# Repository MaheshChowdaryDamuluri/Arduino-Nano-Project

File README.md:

# ⚡ Custom Arduino Nano Compatible PCB Design Project

Welcome to the official repository for the **Custom Arduino Nano Hardware Clone** project. This repository houses the full programmatic schematic blueprints, advanced multi-layer stackup routing configurations, and fabrication-ready source materials engineered entirely within the KiCad design suite. 

Unlike a standard commercial breakout board, this implementation optimizes power rail stability, enhances differential signal impedance, and introduces precise physical test points for desktop diagnostic verification.

---

## 📐 1. Technical System Architecture

The hardware architecture systematically translates your top-level project settings into specialized component zones designed to reduce trace length and eliminate unwanted parasitic loops:

### 🧠 Core Microcontroller Node (`Arduino nano.kicad_sch`)
* **Processor Unit:** Features a high-performance 8-bit AVR microcontroller housed in an ultra-compact, surface-mount **QFN-32** package footprint.
* **System Clock:** Driven by a precision **16MHz ceramic resonator** (`Murata CSTNE`) to ensure predictable, jitter-free code execution timing.
* **ICSP Header Array:** Breaks out a standard 3-pin In-Circuit Serial Programming (ICSP) interface alongside standard vertical female pin-socket strips for effortless external bootloader flashing and pin mapping.

### 🔌 USB Telemetry & Serial Interface
* **Interface Bridge:** Built around the rugged **FT232RL SSOP-28** USB-to-Serial converter chip, delivering bulletproof stability over long debugging sessions.
* **Upstream Protection:** Protects your computer's USB controller using a resettable surface-mount **0603 Polyfuse** to clamp unexpected short-circuits instantly.
* **Differential Signaling:** Routes raw data lines using precise trace spacing down to test pads (`TP1` and `TP2`) for real-time oscilloscope signal inspection.

### ⚡ Power Supply & Linear Regulation Network
* **DC-DC Step-Down:** Incorporates a dedicated low-dropout (LDO) **LM1117MP-5.0 fixed linear regulator** in a robust SOT-223 package.
* **Filtering Topology:** Employs a multi-stage decoupling matrix combining polarized Tantalum bulk smoothing capacitors ($4.7\mu\text{F}$) with high-frequency $100\text{nF}$ ceramic filtering passives positioned right at the power input boundaries to block supply ripple spikes.
* **Input Isolation:** Implements an internal Schottky reverse-voltage protection diode to safely manage power handover between the external input pin and the desktop USB port.

---

## 🛠️ 2. PCB Layer Stackup & Layout Disciplines

The layout database shifts away from legacy double-sided prototyping to a high-speed **4-layer PCB architecture** configured inside the board setup:

1. **Top Layer (`F.Cu`):** High-density component landing networks and primary signal trace breakouts.
2. **Inner Layer 1 (`In1.Cu`):** Solid Ground Plane (`GND`) serving as a low-impedance return path to significantly reduce EM emissions.
3. **Inner Layer 2 (`In2.Cu`):** Specialized Power Grid distribution plane handling multiple system voltages.
4. **Bottom Layer (`B.Cu`):** Secondary routing pathways and clear status indicators.

* **🎨 Solder Mask Aesthetic:** Formatted for a sleek, premium **Blue Solder Mask** application over high-grade FR4 core material.
* **🚦 Status LEDs:** Incorporates four surface-mount visual telemetry indicators (Yellow for Power tracking, Green for Reset lines, and Red/Green options for system notifications).

---

## 📋 3. Project Bill of Materials (BOM)

| Designator | Component Quantity | Component Value | Package Footprint | Purpose / Function |
| :--- | :---: | :--- | :--- | :--- |
| **U1** | 1 | MCU Core Chip | QFN-32-1EP (5x5mm) | Primary Microcontroller Core |
| **U3** | 1 | FT232RL | SSOP-28_5.3x10.2mm | USB to Serial Communication Bridge |
| **U2** | 1 | LM1117MP-5.0 | SOT-223-3 (TabPin2) | +5V Low-Dropout Regulator |
| **F1** | 1 | Polyfuse (0603) | D_0603_1608Metric | Resettable Overcurrent Protection |
| **Y1** | 1 | 16MHz Resonator | CSTxExxV-3Pin (3.0x1.1mm) | Core Clock Source Oscillator |
| **J1** | 1 | USB_B_Mini | USB_Mini-B_Horizontal | System Power & Programming Interface |
| **SW1** | 1 | SW_Push | Panasonic_EVQPUK_EVQPUB | Master Hardware Reset Button |
| **C4, C9** | 2 | 4u7_16V | CP_EIA-3216-10_Kemet-I | Polarized Tantalum Smoothing Capacitors |
| **C1, C2, C5, C6** | 4 | 1u | C_0603_1608Metric | Ceramic Decoupling Passives |
| **C3, C7, C8, C10** | 4 | 100n | C_0603_1608Metric | High-Frequency Bypass Capacitors |
| **R1 - R7** | 7 | 1k | D_0603_1608Metric | Current Limiting Resistors |
| **D1 - D5** | 5 | LED Colors | LED_0805_2012Metric | Telemetry & Visual Status Indicators |

---

## 📂 4. Repository File Directory
```text
├── Arduino nano.kicad_pro    # Master project settings linking schematics & board layers
├── Arduino nano.kicad_sch    # Top-level interactive hardware electrical schema
├── Arduino nano.kicad_pcb    # Completed physical 4-layer trace layout matrix
├── Arduino nano.kicad_prl    # Project local display preferences & monitor settings
├── .gitignore                # Automatically generated rule patterns filtering out bak files
└── LICENSE                   # MIT Open-Source Hardware Licensing certification

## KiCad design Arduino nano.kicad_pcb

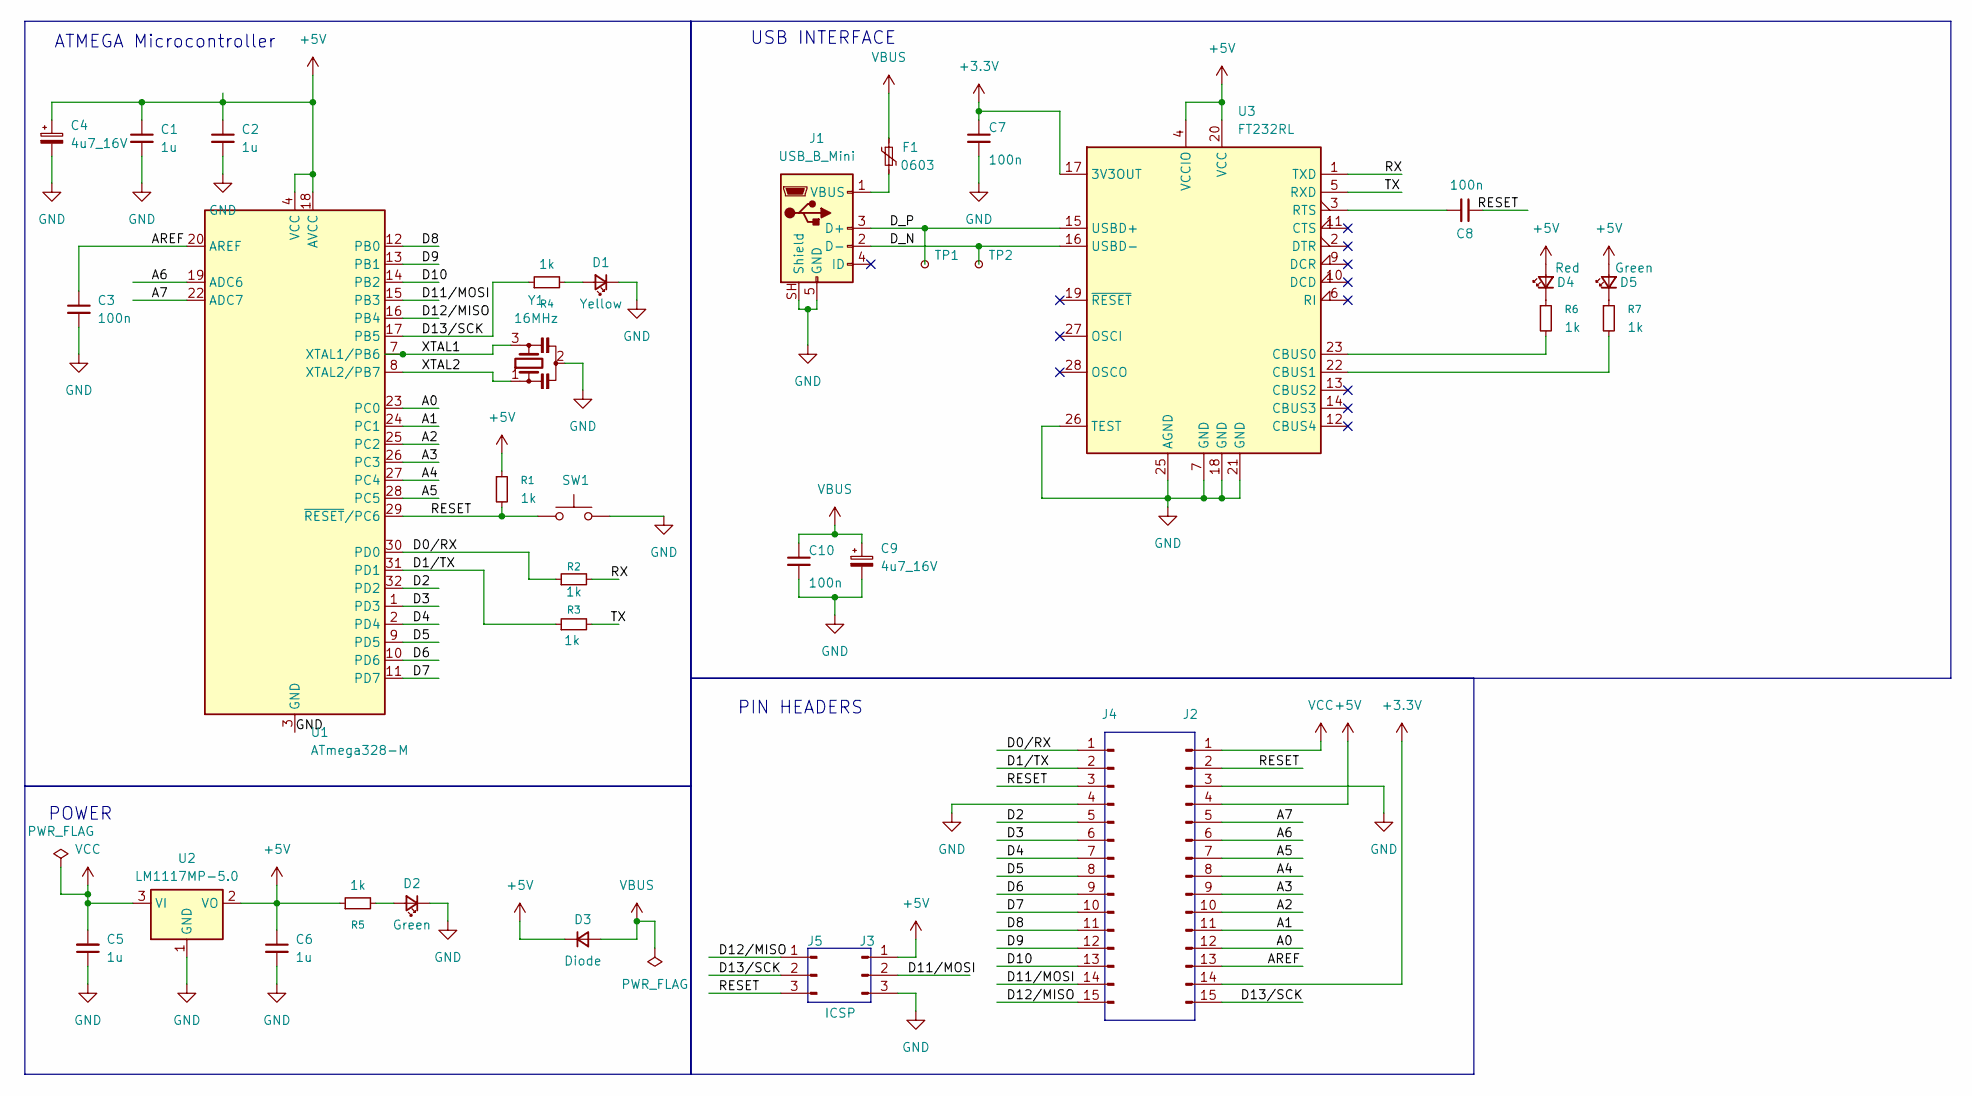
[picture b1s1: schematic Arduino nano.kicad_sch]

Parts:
C1, C2, C5, C6: 1u; C_0603_1608Metric
C3, C7, C8, C10: 100n; C_0603_1608Metric
C4, C9: 4u7_16V; CP_EIA-3216-10_Kemet-I
D1: Yellow; LED_0805_2012Metric
D2, D5: Green; LED_0805_2012Metric
D3: Diode; D_MicroSMP_AK
D4: Red; LED_0805_2012Metric
F1: 0603; D_0603_1608Metric
J1: USB_B_Mini; USB_Mini-B_Wuerth_65100516121_Horizontal
J2, J4: Conn_01x15_Pin; PinSocket_1x15_P2.54mm_Vertical
J3: ICSP; PinHeader_1x03_P2.54mm_Vertical
J5: Conn_01x03_Pin; PinHeader_1x03_P2.54mm_Vertical
R1, R2, R3, R4, R5, R6, R7: 1k; D_0603_1608Metric
SW1: SW_Push; Panasonic_EVQPUK_EVQPUB
TP1, TP2: TestPoint_Small; TestPoint_Pad_D1.0mm
U1: ATmega328-M; QFN-32-1EP_5x5mm_P0.5mm_EP3.1x3.1mm
U2: LM1117MP-5.0; SOT-223-3_TabPin2
U3: FT232RL; SSOP-28_5.3x10.2mm_P0.65mm
Y1: 16MHz; Resonator_SMD_Murata_CSTxExxV-3Pin_3.0x1.1mm

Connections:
+3.3V: C7.1, J2.14, U3.17 (3V3OUT)
+5V: C1.1, C2.1, C4.1, C6.1, D3.1 (K), D4.2 (A), D5.2 (A), J2.4, J3.1, R1.1, R5.1, U1.4 (VCC), U1.6 (VCC), U1.18 (AVCC), U2.2 (VO), U3.4 (VCCIO), U3.20 (VCC)
/A0: J2.12, U1.23 (PC0)
/A1: J2.11, U1.24 (PC1)
/A2: J2.10, U1.25 (PC2)
/A3: J2.9, U1.26 (PC3)
/A4: J2.8, U1.27 (PC4)
/A5: J2.7, U1.28 (PC5)
/A6: J2.6, U1.19 (ADC6)
/A7: J2.5, U1.22 (ADC7)
/AREF: C3.1, J2.13, U1.20 (AREF)
/D0/RX: J4.1, R2.1, U1.30 (PD0)
/D1/TX: J4.2, R3.1, U1.31 (PD1)
/D2: J4.5, U1.32 (PD2)
/D3: J4.6, U1.1 (PD3)
/D4: J4.7, U1.2 (PD4)
/D5: J4.8, U1.9 (PD5)
/D6: J4.9, U1.10 (PD6)
/D7: J4.10, U1.11 (PD7)
/D8: J4.11, U1.12 (PB0)
/D9: J4.12, U1.13 (PB1)
/D10: J4.13, U1.14 (PB2)
/D11/MOSI: J3.2, J4.14, U1.15 (PB3)
/D12/MISO: J4.15, J5.1, U1.16 (PB4)
/D13/SCK: J2.15, J5.2, R4.1, U1.17 (PB5)
/D_N: J1.2 (D-), TP2.1, U3.16 (USBD-)
/D_P: J1.3 (D+), TP1.1, U3.15 (USBD+)
/RESET: C8.1, J2.2, J4.3, J5.3, R1.2, SW1.1, U1.29 (~RESET/PC6)
/RX: R2.2, U3.1 (TXD)
/TX: R3.2, U3.5 (RXD)
/XTAL1: U1.7 (XTAL1/PB6), Y1.3
/XTAL2: U1.8 (XTAL2/PB7), Y1.1
GND: C1.2, C2.2, C3.2, C4.2, C5.1, C6.2, C7.2, C9.2, C10.2, D1.1 (K), D2.1 (K), J1.5 (GND), J1.6 (Shield), J1.SH (Shield), J2.3, J3.3, J4.4, SW1.2, U1.3 (GND), U1.5 (GND), U1.21 (GND), U1.33 (GND), U2.1 (GND), U3.7 (GND), U3.18 (GND), U3.21 (GND), U3.25 (AGND), U3.26 (TEST), Y1.2
unnamed: D1.2 (A), R4.2
unnamed: D2.2 (A), R5.2
unnamed: D4.1 (K), R6.1
unnamed: D5.1 (K), R7.1
unnamed: F1.2, J1.1 (VBUS)
unnamed: R6.2, U3.23 (CBUS0)
unnamed: R7.2, U3.22 (CBUS1)
unnamed: C8.2, U3.3 (RTS)
VBUS: C9.1, C10.1, D3.2 (A), F1.1
VCC: C5.2, J2.1, U2.3 (VI)

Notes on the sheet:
ATMEGA Microcontroller
PIN HEADERS
POWER
USB INTERFACE

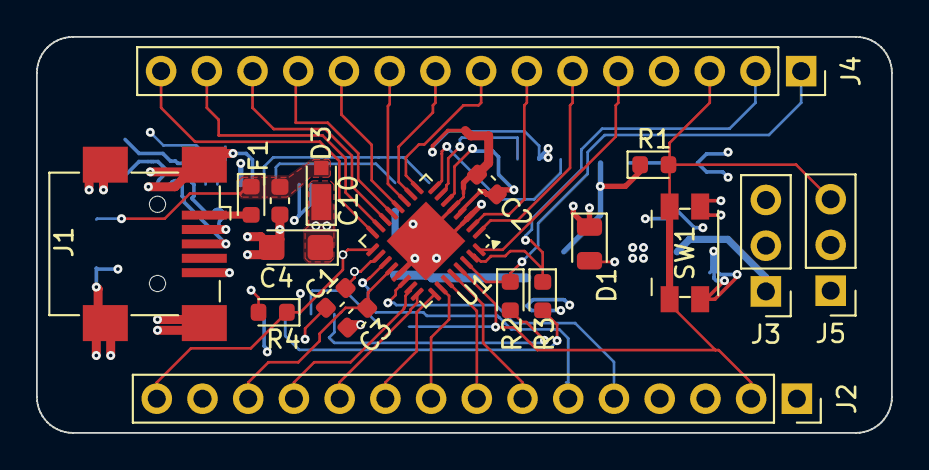
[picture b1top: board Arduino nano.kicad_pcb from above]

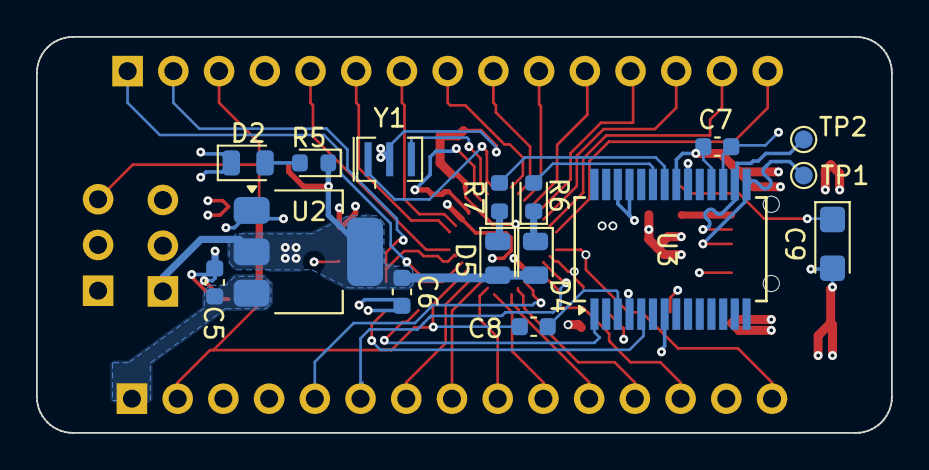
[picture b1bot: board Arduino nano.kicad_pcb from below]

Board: 4 copper layers, 47.5 x 22.0 mm, 35 parts (16 on the bottom side), 43 nets.

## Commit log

2026-06-29 Initial commit: Added Arduino Nano schematic, 4-layer stackup layout, and project configurations
2026-06-29 Create LICENSE
